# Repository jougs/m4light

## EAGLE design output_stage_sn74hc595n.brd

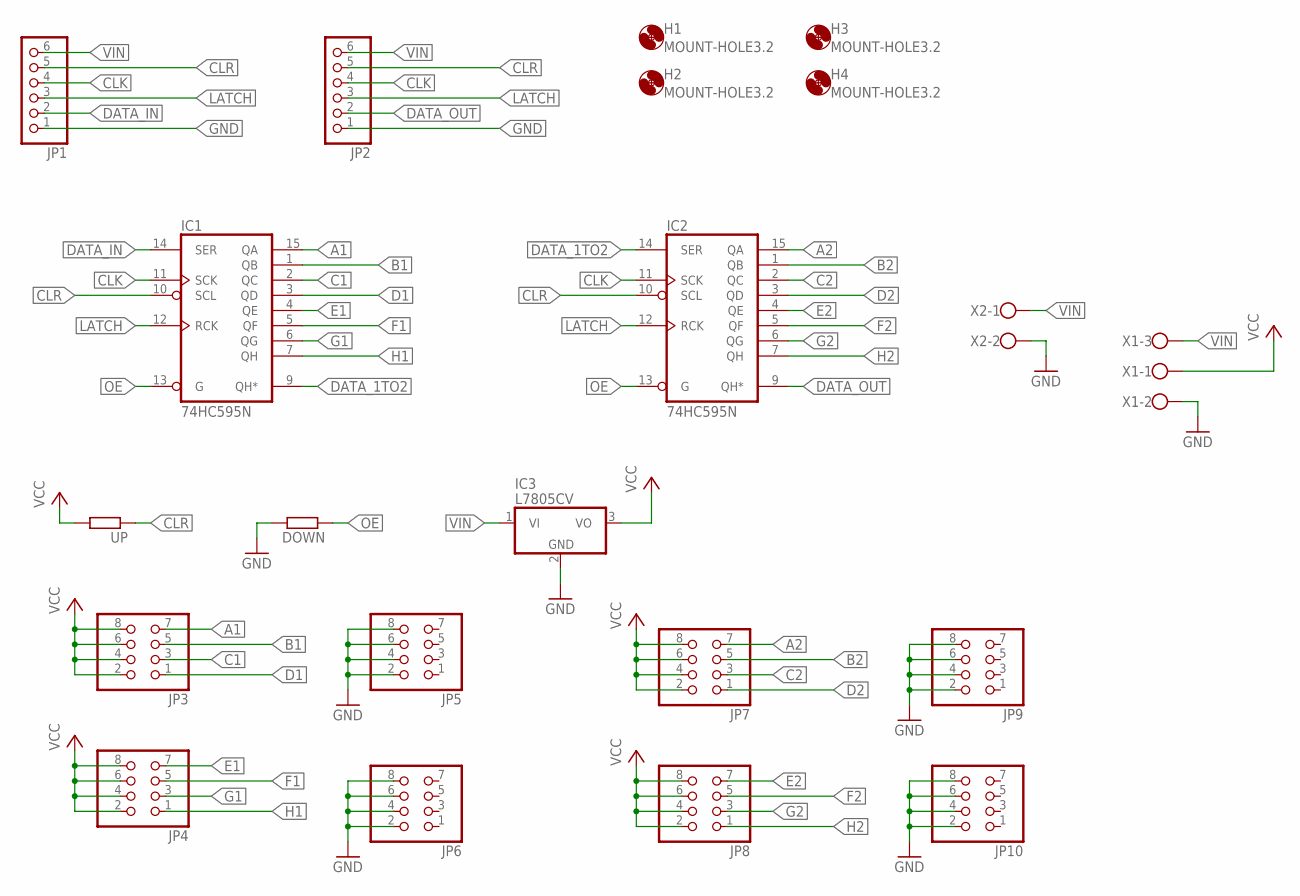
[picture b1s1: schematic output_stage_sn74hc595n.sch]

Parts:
DOWN: R-EU_0207/10; 0207/10
H1, H2, H3, H4: MOUNT-HOLE3.2; 3,2
IC1, IC2: 74HC595N; DIL16
IC3: L7805CV; TO220V
JP1, JP2: PINHD-1X6; 1X06
JP3, JP4, JP5, JP6, JP7, JP8, JP9, JP10: PINHD-2X4; 2X04
UP: R-EU_0207/10; 0207/10
X1: W237-103
X2: W237-102

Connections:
A1: IC1.15 (QA), JP3.7
A2: IC2.15 (QA), JP7.7
B1: IC1.1 (QB), JP3.5
B2: IC2.1 (QB), JP7.5
C1: IC1.2 (QC), JP3.3
C2: IC2.2 (QC), JP7.3
CLK: IC1.11 (SCK), IC2.11 (SCK), JP1.4, JP2.4
CLR: IC1.10 (SCL), IC2.10 (SCL), JP1.5, JP2.5, UP.1
D1: IC1.3 (QD), JP3.1
D2: IC2.3 (QD), JP7.1
DATA_1TO2: IC1.9 (QH*), IC2.14 (SER)
DATA_IN: IC1.14 (SER), JP1.2
DATA_OUT: IC2.9 (QH*), JP2.2
E1: IC1.4 (QE), JP4.7
E2: IC2.4 (QE), JP8.7
F1: IC1.5 (QF), JP4.5
F2: IC2.5 (QF), JP8.5
G1: IC1.6 (QG), JP4.3
G2: IC2.6 (QG), JP8.3
GND: DOWN.2, IC1.8 (GND), IC2.8 (GND), IC3.2 (GND), JP1.1, JP2.1, JP5.2, JP5.4, JP5.6, JP5.8, JP6.2, JP6.4, JP6.6, JP6.8, JP9.2, JP9.4, JP9.6, JP9.8, JP10.2, JP10.4, JP10.6, JP10.8, X1.2, X2.2
H1: IC1.7 (QH), JP4.1
H2: IC2.7 (QH), JP8.1
LATCH: IC1.12 (RCK), IC2.12 (RCK), JP1.3, JP2.3
OE: DOWN.1, IC1.13 (G), IC2.13 (G)
VCC: IC1.16 (VCC), IC2.16 (VCC), IC3.3 (VO), JP3.2, JP3.4, JP3.6, JP3.8, JP4.2, JP4.4, JP4.6, JP4.8, JP7.2, JP7.4, JP7.6, JP7.8, JP8.2, JP8.4, JP8.6, JP8.8, UP.2, X1.1
VIN: IC3.1 (VI), JP1.6, JP2.6, X1.3, X2.1

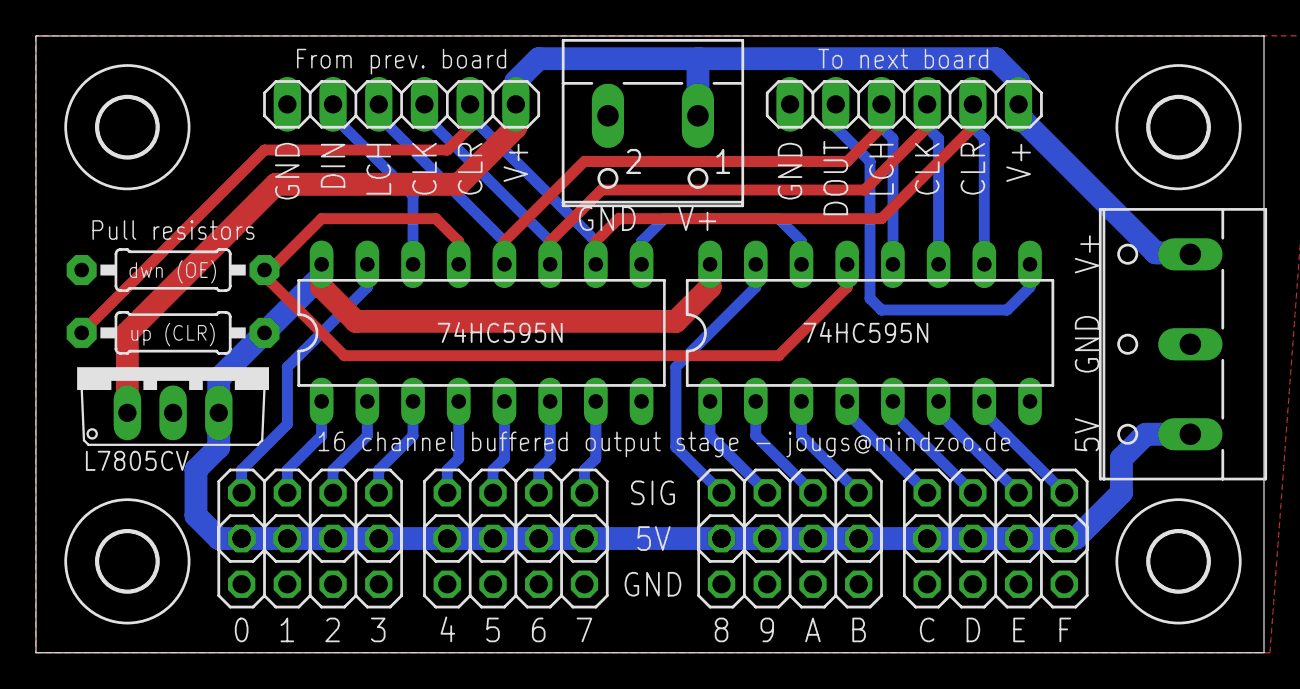
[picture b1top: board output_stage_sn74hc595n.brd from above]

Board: 2 copper layers, 68.2 x 34.3 mm, 21 parts (0 on the bottom side), 26 nets.

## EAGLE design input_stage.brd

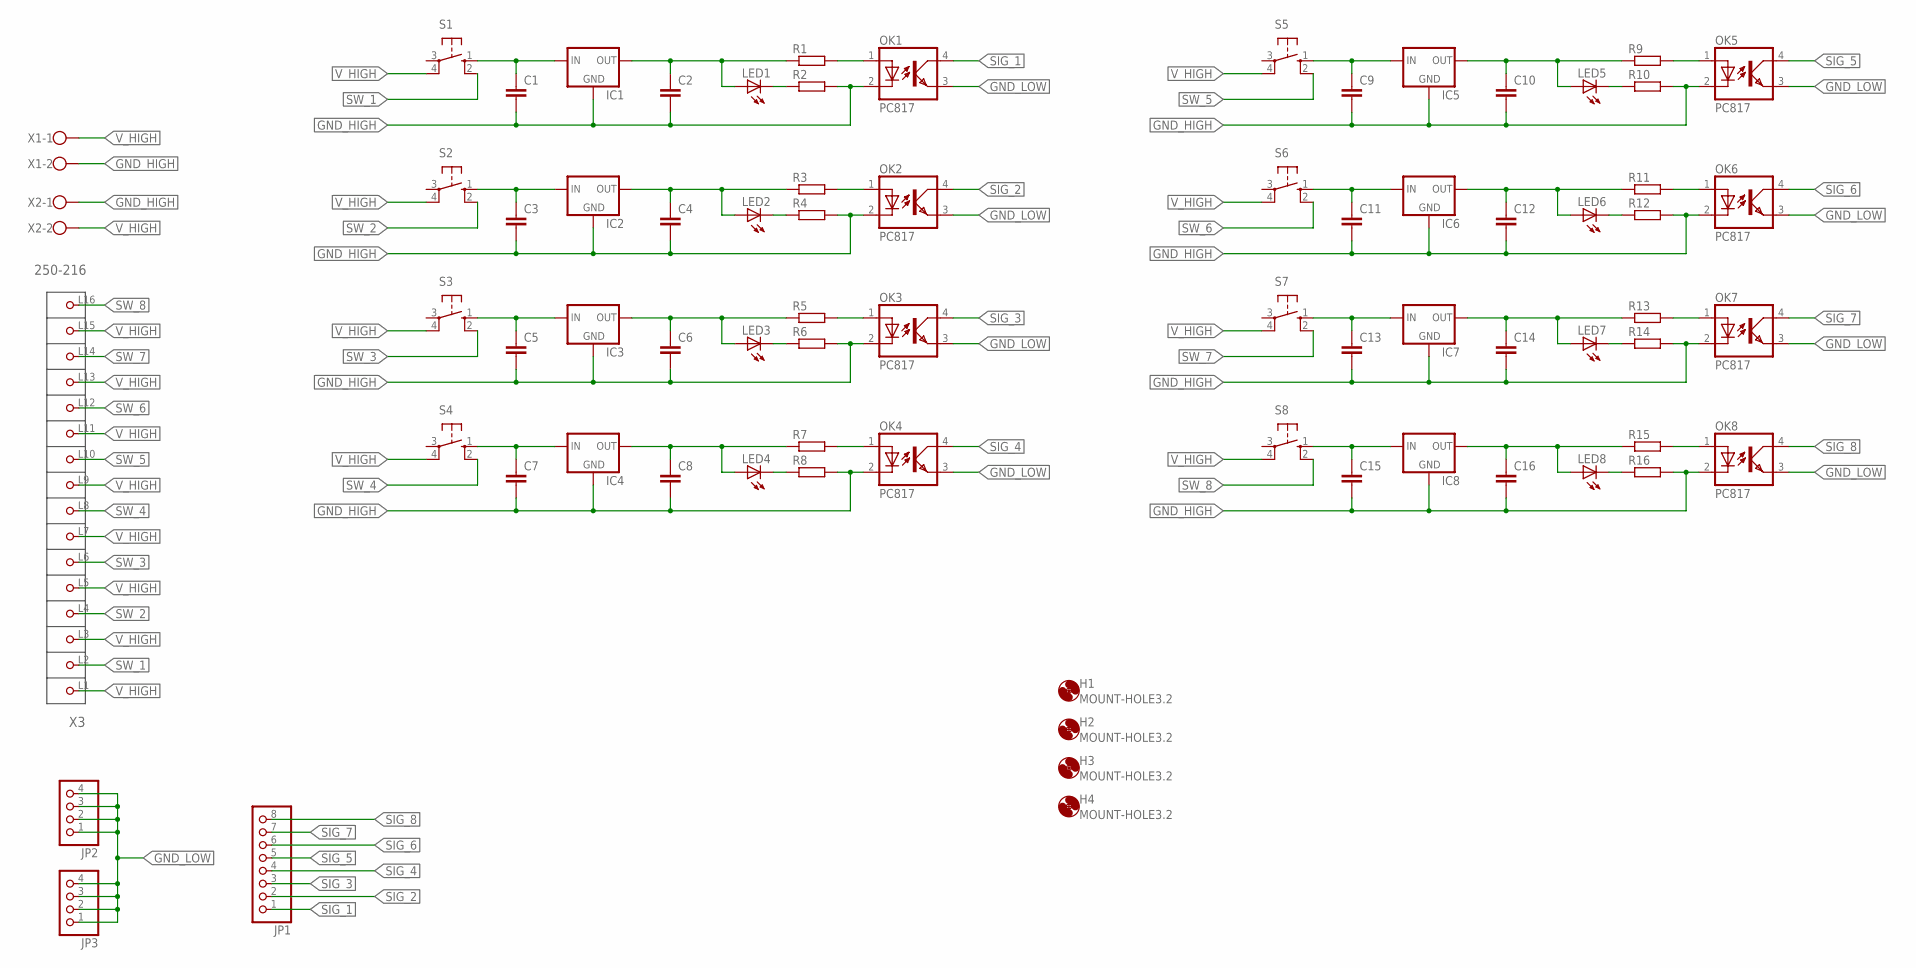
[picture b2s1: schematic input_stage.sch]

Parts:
C1, C2, C3, C4, C5, C6, C7, C8, C9, C10, C11, C12, C13, C14, C15, C16: C-EU050-024X044; C050-024X044
H1, H2, H3, H4: MOUNT-HOLE3.2; 3,2
IC1, IC2, IC3, IC4, IC5, IC6, IC7, IC8: 78LXX
JP1: PINHD-1X8; 1X08
JP2, JP3: PINHD-1X4; 1X04
LED1, LED2, LED3, LED4, LED5, LED6, LED7, LED8: LED3MM
OK1, OK2, OK3, OK4, OK5, OK6, OK7, OK8: PC817; DIL04
R1, R2, R3, R4, R5, R6, R7, R8, R9, R10, R11, R12, R13, R14, R15, R16: R-EU_0207/10; 0207/10
S1, S2, S3, S4, S5, S6, S7, S8: 10-XX; B3F-10XX
X1, X2: W237-102
X3: 250-216; P-250-216

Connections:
GND_HIGH: C1.2, C2.2, C3.2, C4.2, C5.2, C6.2, C7.2, C8.2, C9.2, C10.2, C11.2, C12.2, C13.2, C14.2, C15.2, C16.2, IC1.GND, IC2.GND, IC3.GND, IC4.GND, IC5.GND, IC6.GND, IC7.GND, IC8.GND, OK1.2 (C), OK2.2 (C), OK3.2 (C), OK4.2 (C), OK5.2 (C), OK6.2 (C), OK7.2 (C), OK8.2 (C), R2.2, R4.2, R6.2, R8.2, R10.2, R12.2, R14.2, R16.2, X1.2, X2.1
GND_LOW: JP2.1, JP2.2, JP2.3, JP2.4, JP3.1, JP3.2, JP3.3, JP3.4, OK1.3 (EMIT), OK2.3 (EMIT), OK3.3 (EMIT), OK4.3 (EMIT), OK5.3 (EMIT), OK6.3 (EMIT), OK7.3 (EMIT), OK8.3 (EMIT)
unnamed: OK1.1 (A), R1.2
unnamed: C2.1, IC1.OUT, LED1.A, R1.1
unnamed: C1.1, IC1.IN, S1.1 (S)
unnamed: LED1.K (C), R2.1
unnamed: OK4.1 (A), R7.2
unnamed: OK2.1 (A), R3.2
unnamed: C8.1, IC4.OUT, LED4.A, R7.1
unnamed: LED4.K (C), R8.1
unnamed: OK5.1 (A), R9.2
unnamed: C10.1, IC5.OUT, LED5.A, R9.1
unnamed: LED5.K (C), R10.1
unnamed: OK6.1 (A), R11.2
unnamed: C3.1, IC2.IN, S2.1 (S)
unnamed: C12.1, IC6.OUT, LED6.A, R11.1
unnamed: C5.1, IC3.IN, S3.1 (S)
unnamed: LED6.K (C), R12.1
unnamed: C7.1, IC4.IN, S4.1 (S)
unnamed: OK7.1 (A), R13.2
unnamed: C15.1, IC8.IN, S8.1 (S)
unnamed: C4.1, IC2.OUT, LED2.A, R3.1
unnamed: LED2.K (C), R4.1
unnamed: C14.1, IC7.OUT, LED7.A, R13.1
unnamed: OK3.1 (A), R5.2
unnamed: C6.1, IC3.OUT, LED3.A, R5.1
unnamed: LED3.K (C), R6.1
unnamed: LED7.K (C), R14.1
unnamed: OK8.1 (A), R15.2
unnamed: C16.1, IC8.OUT, LED8.A, R15.1
unnamed: LED8.K (C), R16.1
unnamed: C13.1, IC7.IN, S7.1 (S)
unnamed: C11.1, IC6.IN, S6.1 (S)
unnamed: C9.1, IC5.IN, S5.1 (S)
SIG_1: JP1.1, OK1.4 (COL)
SIG_2: JP1.2, OK2.4 (COL)
SIG_3: JP1.3, OK3.4 (COL)
SIG_4: JP1.4, OK4.4 (COL)
SIG_5: JP1.5, OK5.4 (COL)
SIG_6: JP1.6, OK6.4 (COL)
SIG_7: JP1.7, OK7.4 (COL)
SIG_8: JP1.8, OK8.4 (COL)
SW_1: S1.2 (S1), X3.L2 (P2)
SW_2: S2.2 (S1), X3.L4 (P4)
SW_3: S3.2 (S1), X3.L6 (P6)
SW_4: S4.2 (S1), X3.L8 (P8)
SW_5: S5.2 (S1), X3.L10 (P10)
SW_6: S6.2 (S1), X3.L12 (P12)
SW_7: S7.2 (S1), X3.L14 (P14)
SW_8: S8.2 (S1), X3.L16 (P16)
V_HIGH: S1.4 (P1), S2.4 (P1), S3.4 (P1), S4.4 (P1), S5.4 (P1), S6.4 (P1), S7.4 (P1), S8.4 (P1), X1.1, X2.2, X3.L1 (P1), X3.L3 (P3), X3.L5 (P5), X3.L7 (P7), X3.L9 (P9), X3.L11 (P11), X3.L13 (P13), X3.L15 (P15)

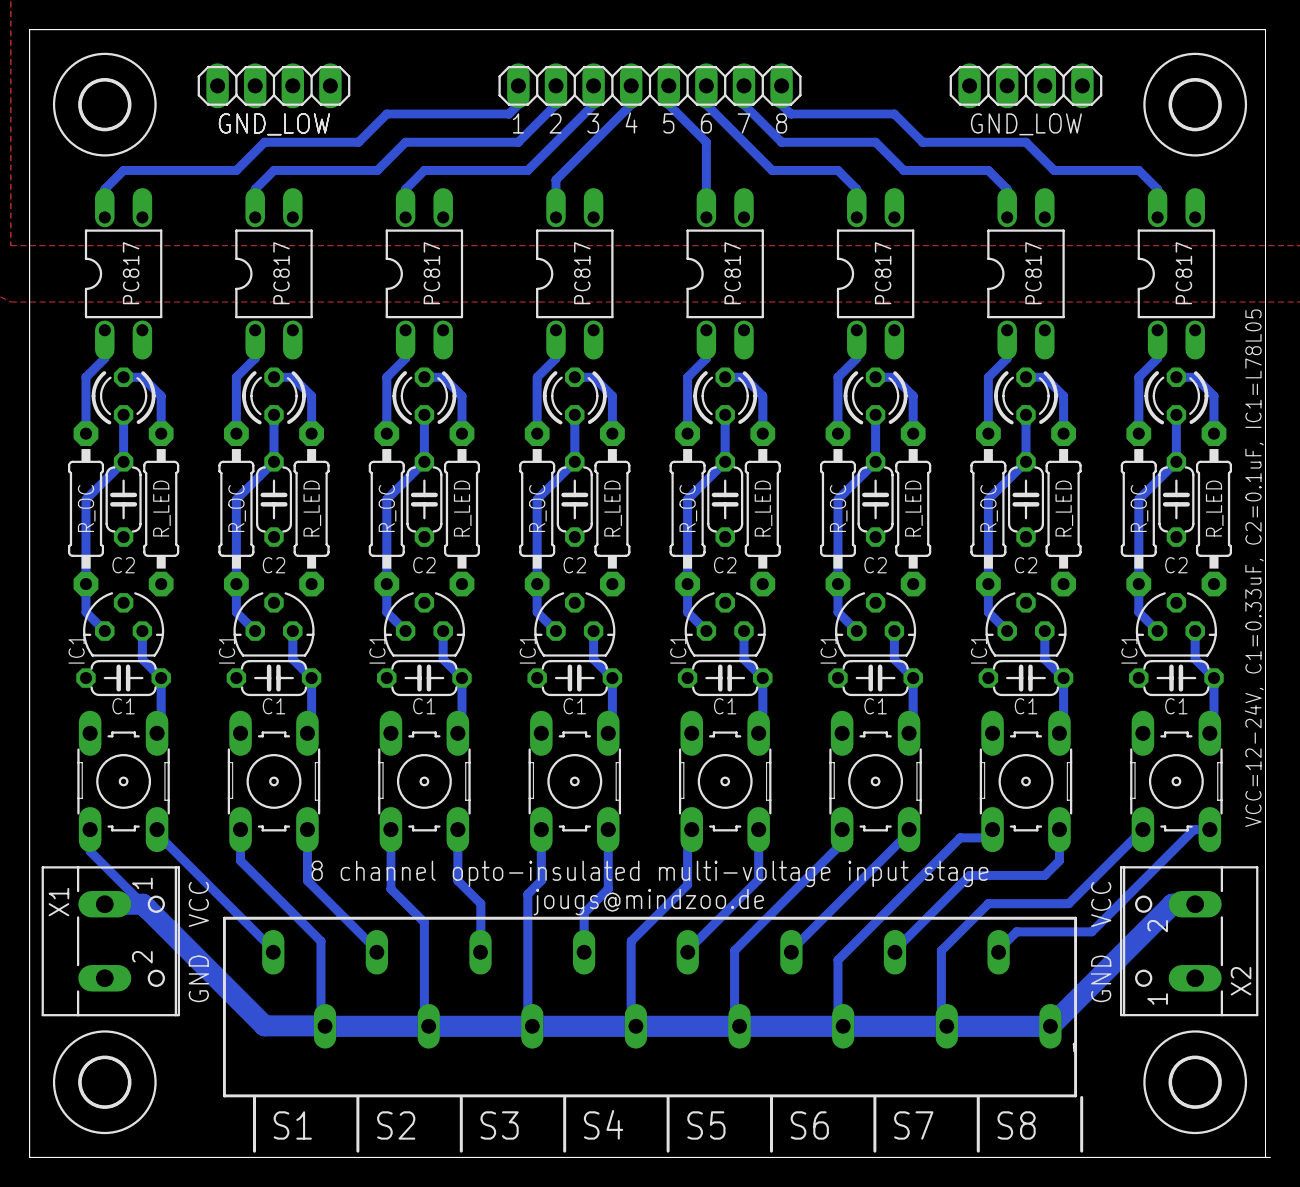
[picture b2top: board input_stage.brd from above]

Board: 2 copper layers, 83.8 x 76.2 mm, 74 parts (0 on the bottom side), 51 nets.

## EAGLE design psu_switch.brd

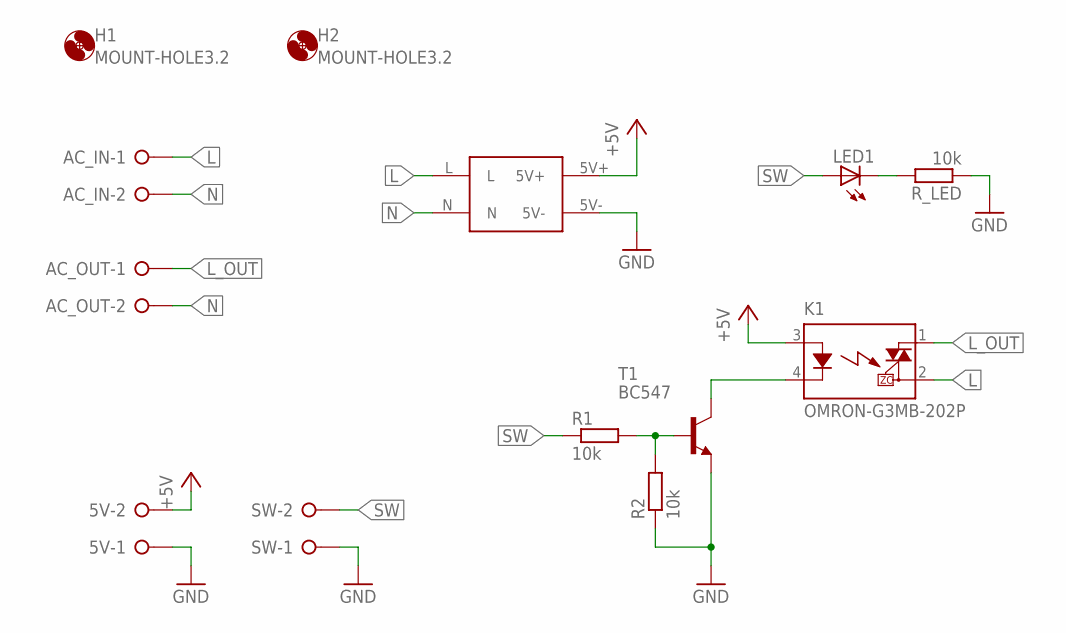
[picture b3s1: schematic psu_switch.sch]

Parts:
5V: W237-02P; W237-132
AC_IN: W237-02P; W237-132
AC_OUT: W237-02P; W237-132
H1, H2: MOUNT-HOLE3.2; 3,2
K1: OMRON-G3MB-202P; OMRON-G3MB-202P-SSR
LED1: LED3MM
R1, R2: 10k; 0207/10
R_LED: 10k; 0207/10
SW: W237-02P; W237-132
T1: BC547; TO92
U$1: 700MA-STEP-DOWN

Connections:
+5V: 5V.2, K1.3 (A), U$1.5V+
GND: 5V.1, R2.1, R_LED.1, SW.1, T1.1 (E), U$1.5V-
L: AC_IN.1, K1.2 (DS2), U$1.L
L_OUT: AC_OUT.1, K1.1 (DS1)
N: AC_IN.2, AC_OUT.2, U$1.N
unnamed: LED1.K (C), R_LED.2
unnamed: K1.4 (K), T1.3 (C)
SW: LED1.A, R1.1, SW.2
SW+: R1.2, R2.2, T1.2 (B)

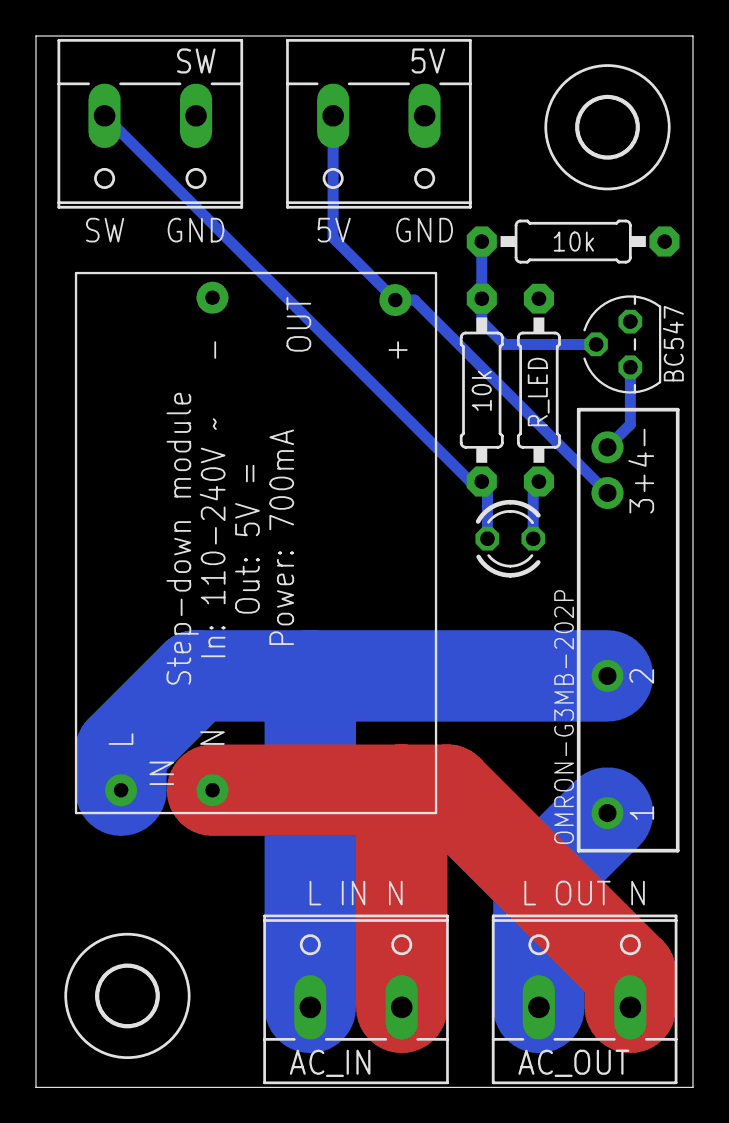
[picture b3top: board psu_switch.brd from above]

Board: 2 copper layers, 36.5 x 58.4 mm, 13 parts (0 on the bottom side), 9 nets.

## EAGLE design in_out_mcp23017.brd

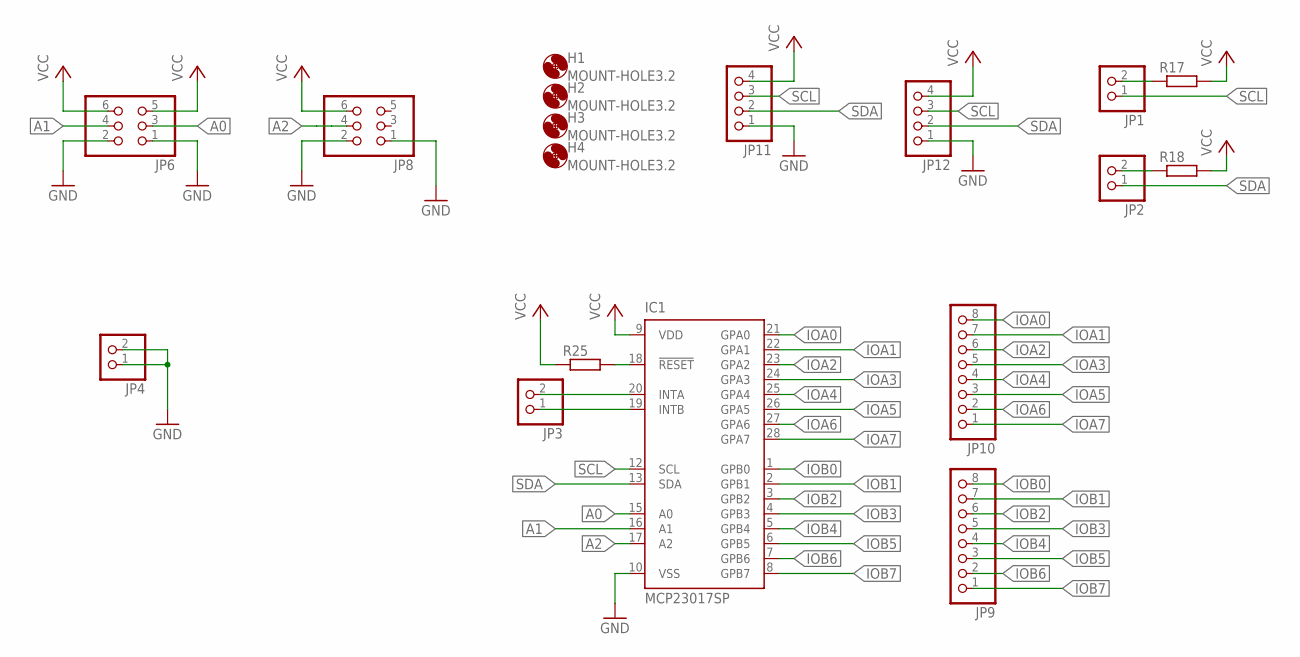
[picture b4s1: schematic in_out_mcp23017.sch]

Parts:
H1, H2, H3, H4: MOUNT-HOLE3.2; 3,2
IC1: MCP23017SP; DIL28-3
JP1, JP2, JP3, JP4: PINHD-1X2; 1X02
JP6, JP8: PINHD-2X3; 2X03
JP9, JP10: PINHD-1X8; 1X08
JP11, JP12: PINHD-1X4; 1X04
R17, R18, R25: R-EU_0207/10; 0207/10

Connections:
A0: IC1.15 (A0), JP6.3
A1: IC1.16 (A1), JP6.4
A2: IC1.17 (A2), JP8.4
GND: IC1.10 (VSS), JP4.1, JP4.2, JP6.1, JP6.2, JP8.1, JP8.2, JP11.1, JP12.1
IOA0: IC1.21 (GPA0), JP10.8
IOA1: IC1.22 (GPA1), JP10.7
IOA2: IC1.23 (GPA2), JP10.6
IOA3: IC1.24 (GPA3), JP10.5
IOA4: IC1.25 (GPA4), JP10.4
IOA5: IC1.26 (GPA5), JP10.3
IOA6: IC1.27 (GPA6), JP10.2
IOA7: IC1.28 (GPA7), JP10.1
IOB0: IC1.1 (GPB0), JP9.8
IOB1: IC1.2 (GPB1), JP9.7
IOB2: IC1.3 (GPB2), JP9.6
IOB3: IC1.4 (GPB3), JP9.5
IOB4: IC1.5 (GPB4), JP9.4
IOB5: IC1.6 (GPB5), JP9.3
IOB6: IC1.7 (GPB6), JP9.2
IOB7: IC1.8 (GPB7), JP9.1
unnamed: IC1.18 (!RESET), R25.2
unnamed: JP2.2, R18.1
unnamed: JP1.2, R17.1
unnamed: IC1.20 (INTA), JP3.2
unnamed: IC1.19 (INTB), JP3.1
SCL: IC1.12 (SCL), JP1.1, JP11.3, JP12.3
SDA: IC1.13 (SDA), JP2.1, JP11.2, JP12.2
VCC: IC1.9 (VDD), JP6.5, JP6.6, JP8.6, JP11.4, JP12.4, R17.2, R18.2, R25.1

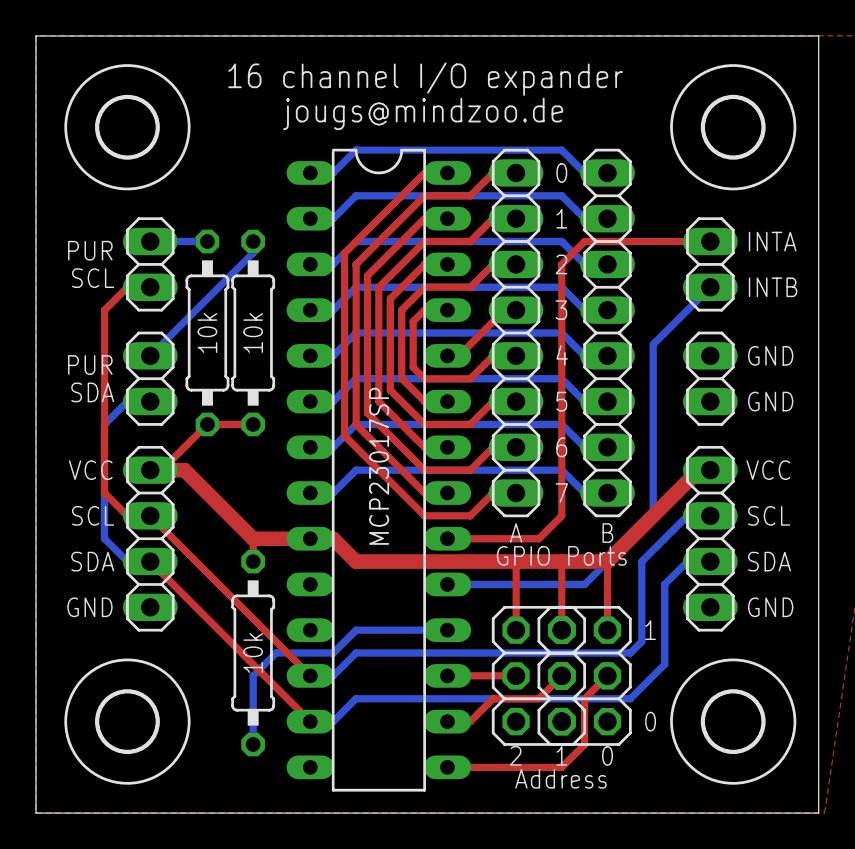
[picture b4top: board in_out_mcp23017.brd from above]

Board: 2 copper layers, 43.5 x 43.2 mm, 18 parts (0 on the bottom side), 28 nets.

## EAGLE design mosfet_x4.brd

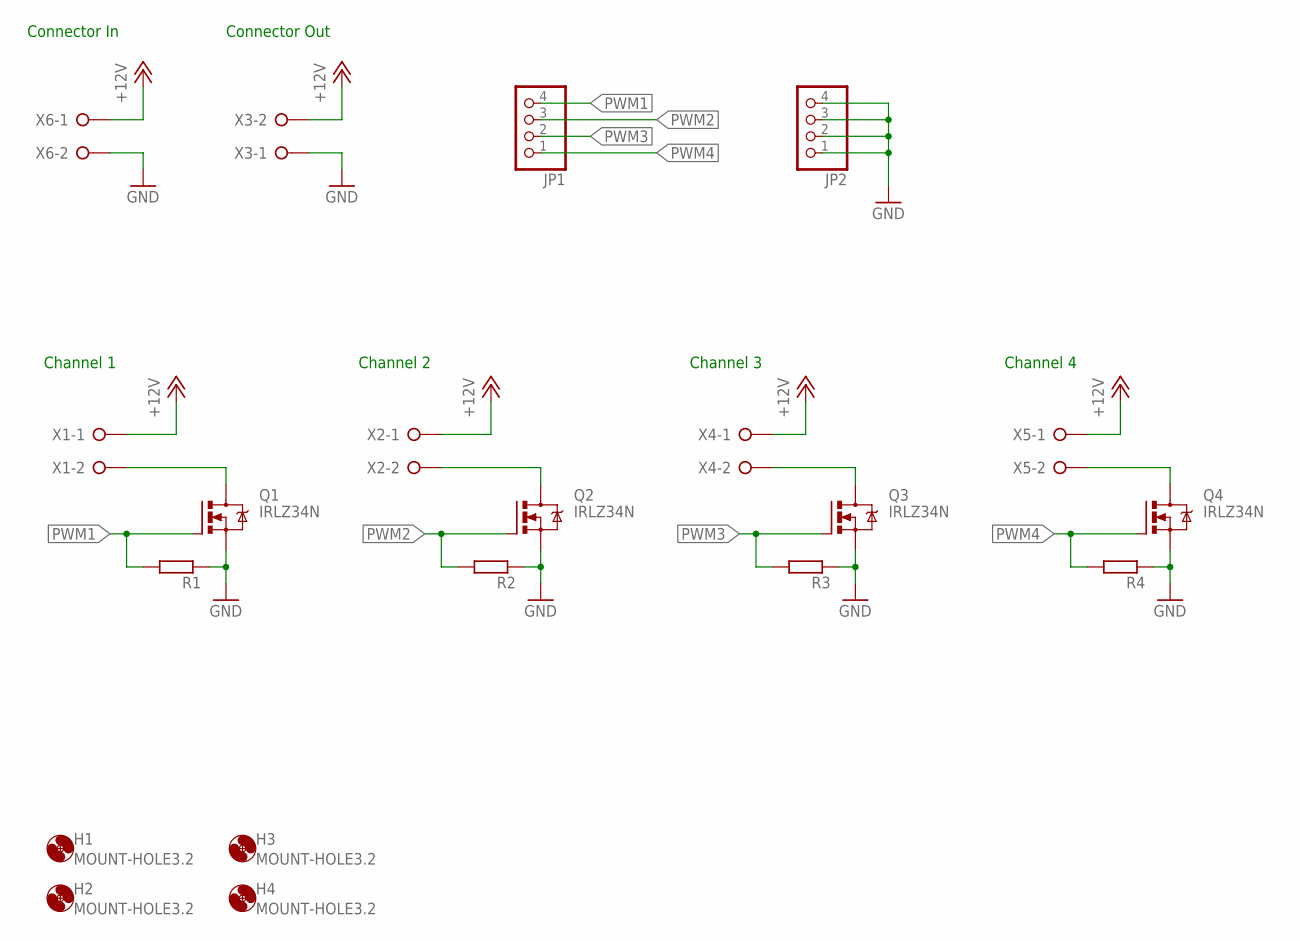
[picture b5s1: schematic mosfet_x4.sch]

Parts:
H1, H2, H3, H4: MOUNT-HOLE3.2; 3,2
JP1, JP2: PINHD-1X4; 1X04
Q1, Q2, Q3, Q4: IRLZ34N; TO220BV
R1, R2, R3, R4: R-EU_0207/10; 0207/10
X1, X2, X3, X4, X5, X6: W237-02P; W237-132

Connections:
+12V: X1.1, X2.1, X3.2, X4.1, X5.1, X6.1
GND: JP2.1, JP2.2, JP2.3, JP2.4, Q1.S, Q2.S, Q3.S, Q4.S, R1.1, R2.1, R3.1, R4.1, X3.1, X6.2
unnamed: Q1.D, X1.2
unnamed: Q2.D, X2.2
unnamed: Q3.D, X4.2
unnamed: Q4.D, X5.2
PWM1: JP1.4, Q1.G, R1.2
PWM2: JP1.3, Q2.G, R2.2
PWM3: JP1.2, Q3.G, R3.2
PWM4: JP1.1, Q4.G, R4.2

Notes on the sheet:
Channel 1
Channel 2
Channel 3
Channel 4
Connector In
Connector Out

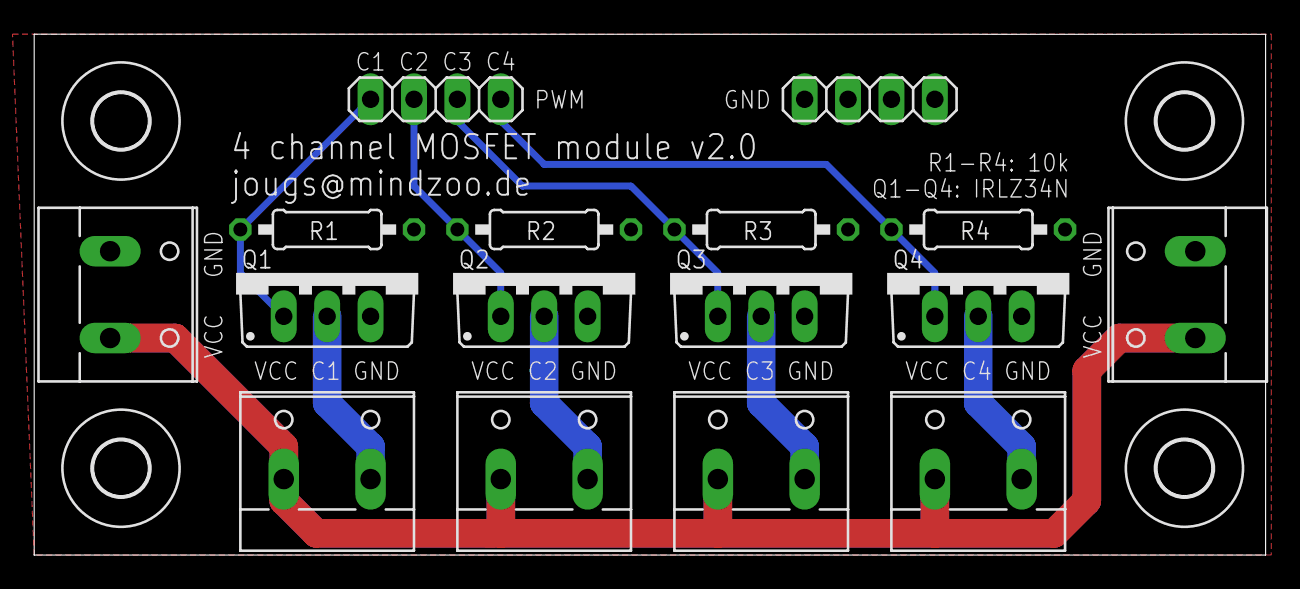
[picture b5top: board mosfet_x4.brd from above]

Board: 2 copper layers, 72.1 x 30.5 mm, 20 parts (0 on the bottom side), 10 nets.

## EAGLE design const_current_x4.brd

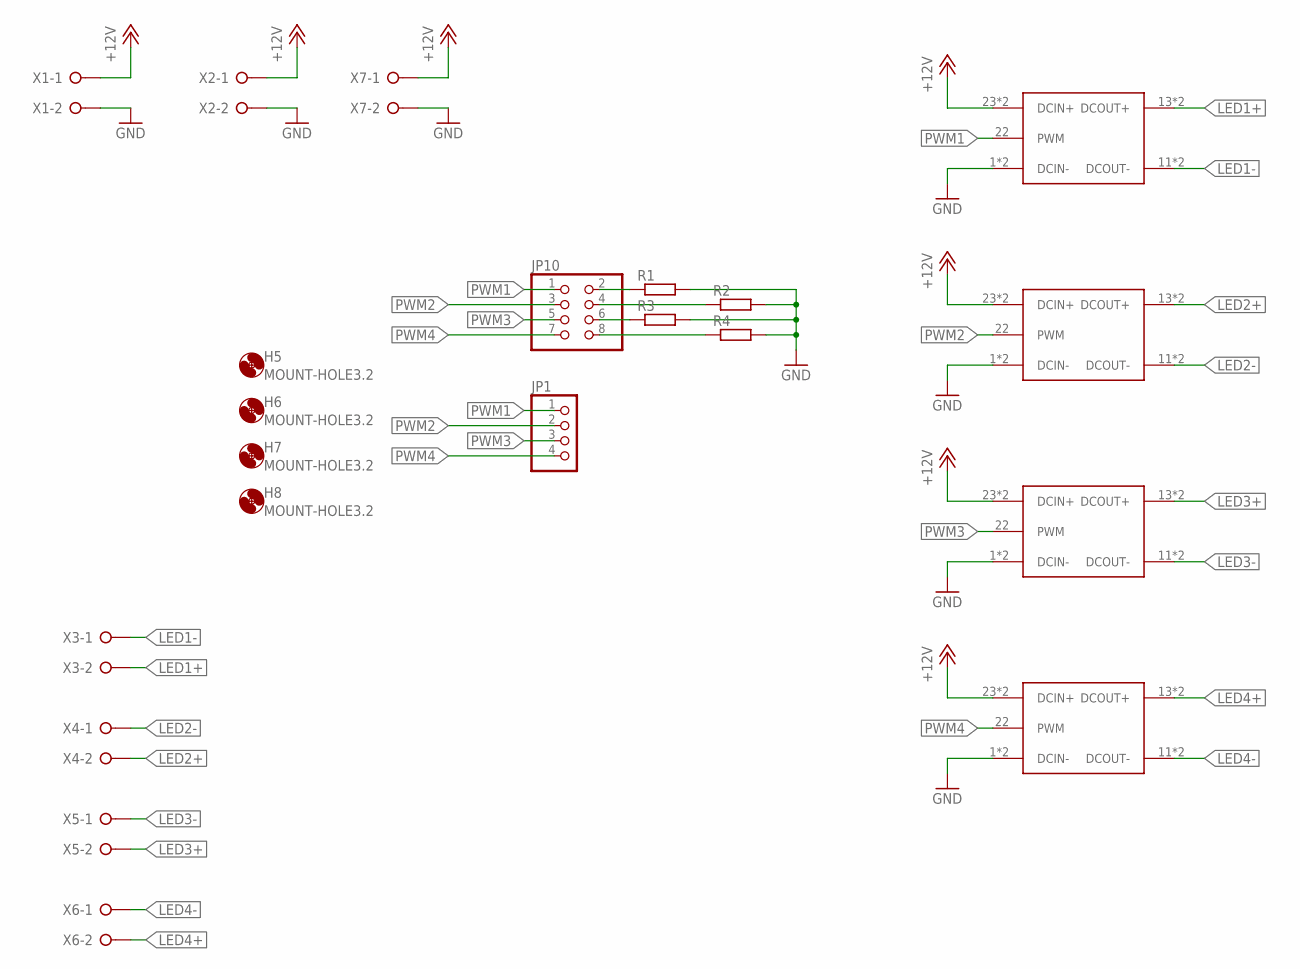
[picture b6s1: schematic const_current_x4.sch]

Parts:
H5, H6, H7, H8: MOUNT-HOLE3.2; 3,2
JP1: PINHD-1X4; 1X04
JP10: PINHD-2X4; 2X04
R1, R2, R3, R4: R-EU_0207/10; 0207/10
U$5, U$6, U$7, U$8: LDD_H
X1, X2, X3, X4, X5, X6, X7: W237-02P; W237-132

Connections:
+12V: U$5.23 (DCIN+), U$5.24 (DCIN+), U$6.23 (DCIN+), U$6.24 (DCIN+), U$7.23 (DCIN+), U$7.24 (DCIN+), U$8.23 (DCIN+), U$8.24 (DCIN+), X1.1, X2.1, X7.1
GND: R1.2, R2.2, R3.2, R4.2, U$5.1 (DCIN-), U$5.2 (DCIN-), U$6.1 (DCIN-), U$6.2 (DCIN-), U$7.1 (DCIN-), U$7.2 (DCIN-), U$8.1 (DCIN-), U$8.2 (DCIN-), X1.2, X2.2, X7.2
LED1+: U$5.13 (DCOUT+), U$5.14 (DCOUT+), X3.2
LED1-: U$5.11 (DCOUT-), U$5.12 (DCOUT-), X3.1
LED2+: U$6.13 (DCOUT+), U$6.14 (DCOUT+), X4.2
LED2-: U$6.11 (DCOUT-), U$6.12 (DCOUT-), X4.1
LED3+: U$7.13 (DCOUT+), U$7.14 (DCOUT+), X5.2
LED3-: U$7.11 (DCOUT-), U$7.12 (DCOUT-), X5.1
LED4+: U$8.13 (DCOUT+), U$8.14 (DCOUT+), X6.2
LED4-: U$8.11 (DCOUT-), U$8.12 (DCOUT-), X6.1
unnamed: JP10.2, R1.1
unnamed: JP10.4, R2.1
unnamed: JP10.6, R3.1
unnamed: JP10.8, R4.1
PWM1: JP1.1, JP10.1, U$5.22 (PWM)
PWM2: JP1.2, JP10.3, U$6.22 (PWM)
PWM3: JP1.3, JP10.5, U$7.22 (PWM)
PWM4: JP1.4, JP10.7, U$8.22 (PWM)

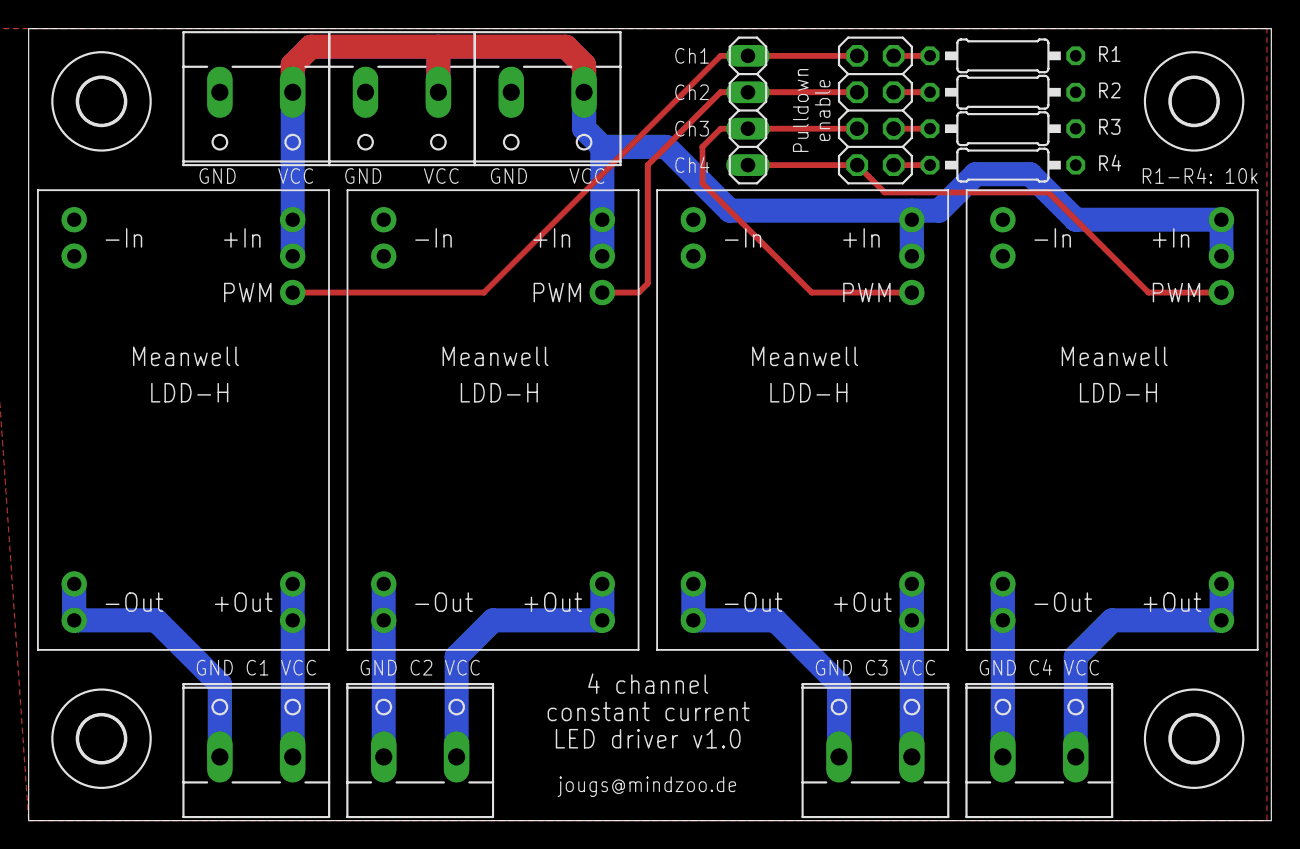
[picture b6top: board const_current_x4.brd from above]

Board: 2 copper layers, 86.7 x 55.2 mm, 21 parts (0 on the bottom side), 18 nets.

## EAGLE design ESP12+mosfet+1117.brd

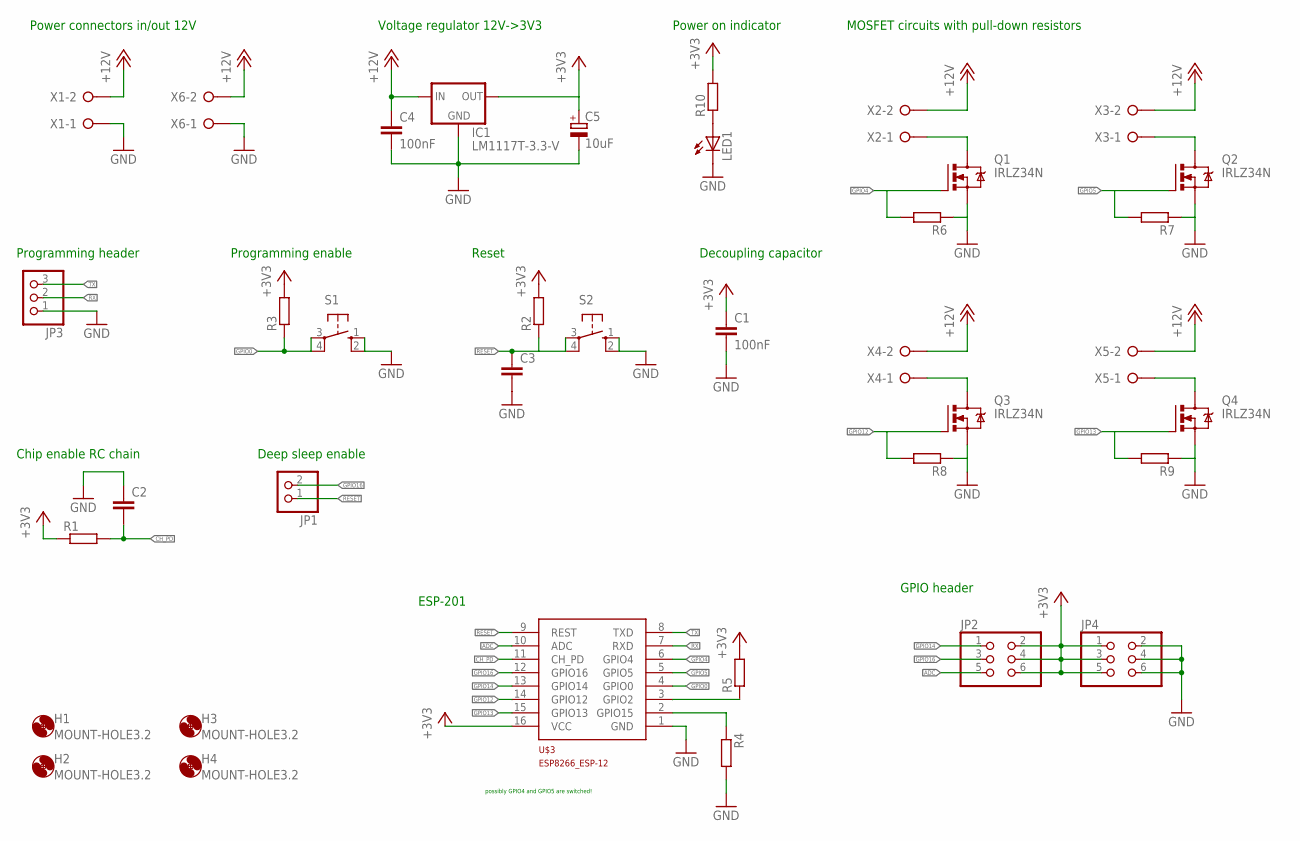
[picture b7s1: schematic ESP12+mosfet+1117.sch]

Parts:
C1, C4: 100nF; C0805
C2, C3: C-EUC0805; C0805
C5: 10uF; E2-4
H1, H2, H3, H4: MOUNT-HOLE3.2; 3,2
IC1: LM1117T-3.3-V; TO220V
JP1: PINHD-1X2; 1X02
JP2, JP4: PINHD-2X3; 2X03
JP3: PINHD-1X3; 1X03
LED1: LED3MM
Q1, Q2, Q3, Q4: IRLZ34N; TO220BV
R1, R2, R3, R4, R5, R6, R7, R8, R9: R-EU_R0805; R0805
R10: R-EU_0207/10; 0207/10
S1, S2: 10-XX; B3F-10XX
U$3: ESP8266_ESP-12; ESP8266-ESP12
X1, X2, X3, X4, X5, X6: W237-02P; W237-132

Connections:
+3V3: C1.1, C5.+, IC1.2 (OUT), JP2.2, JP2.4, JP2.6, JP4.1, JP4.3, JP4.5, R1.1, R2.2, R3.2, R5.2, R10.2, U$3.16 (VCC)
+12V: C4.1, IC1.3 (IN), X1.2, X2.2, X3.2, X4.2, X5.2, X6.2
ADC: JP2.5, U$3.10 (ADC)
CH_PD: C2.2, R1.2, U$3.11 (CH_PD)
GND: C1.2, C2.1, C3.2, C4.2, C5.-, IC1.1 (GND), JP3.1, JP4.2, JP4.4, JP4.6, LED1.K (C), Q1.S, Q2.S, Q3.S, Q4.S, R4.2, R6.1, R7.1, R8.1, R9.1, S1.1 (S), S1.2 (S1), S2.1 (S), S2.2 (S1), U$3.1 (GND), X1.1, X6.1
GPIO0: R3.1, S1.3, S1.4 (P1), U$3.4 (GPIO0)
GPIO1: R5.1, U$3.3 (GPIO2)
GPIO4: Q1.G, R6.2, U$3.6 (GPIO4)
GPIO5: Q2.G, R7.2, U$3.5 (GPIO5)
GPIO12: Q3.G, R8.2, U$3.14 (GPIO12)
GPIO13: Q4.G, R9.2, U$3.15 (GPIO13)
GPIO14: JP2.1, U$3.13 (GPIO14)
GPIO15: R4.1, U$3.2 (GPIO15)
GPIO16: JP1.2, JP2.3, U$3.12 (GPIO16)
unnamed: LED1.A, R10.1
unnamed: Q1.D, X2.1
unnamed: Q2.D, X3.1
unnamed: Q3.D, X4.1
unnamed: Q4.D, X5.1
RESET: C3.1, JP1.1, R2.1, S2.3, S2.4 (P1), U$3.9 (REST)
RX: JP3.2, U$3.7 (RXD)
TX: JP3.3, U$3.8 (TXD)

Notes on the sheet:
Power connectors in/out 12V
Voltage regulator 12V->3V3
Decoupling capacitor
Programming header
Chip enable RC chain
Programming enable
ESP-201
GPIO header
Reset
possibly GPIO4 and GPIO5 are switched!
Deep sleep enable
Power on indicator
MOSFET circuits with pull-down resistors

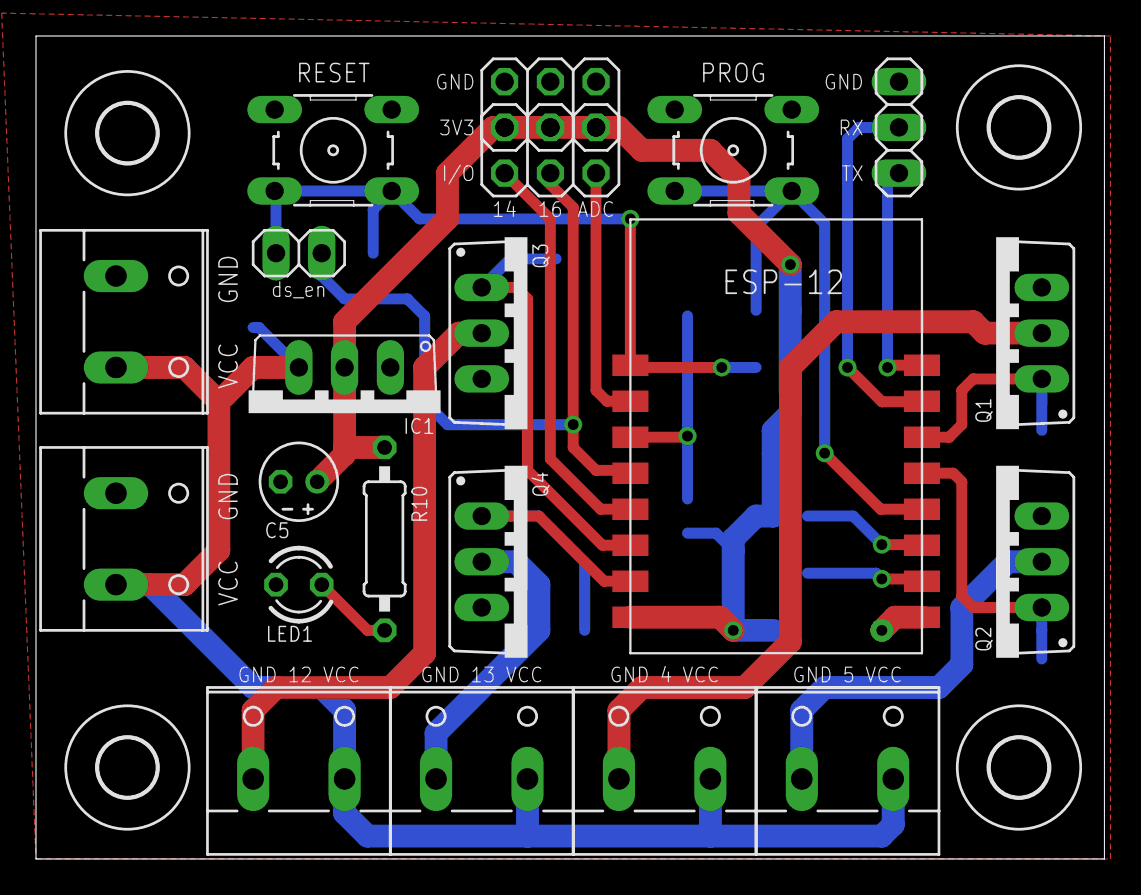
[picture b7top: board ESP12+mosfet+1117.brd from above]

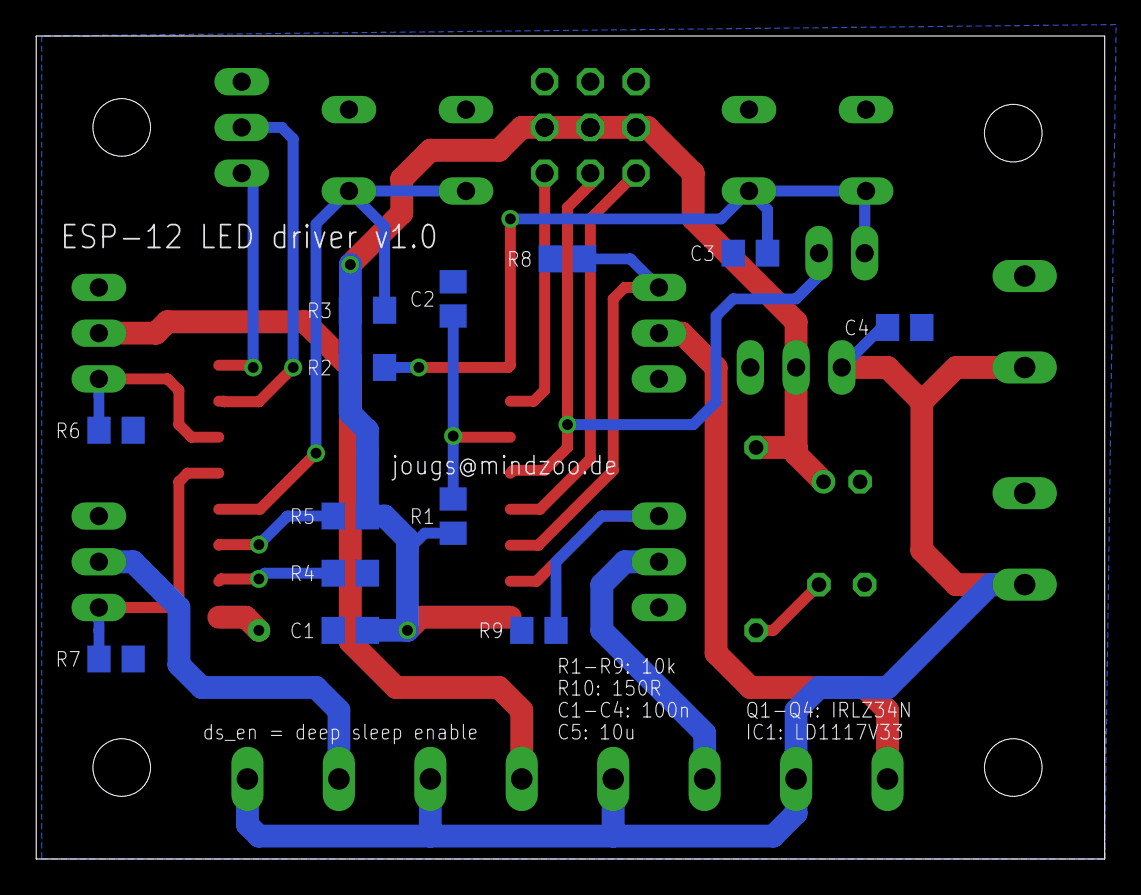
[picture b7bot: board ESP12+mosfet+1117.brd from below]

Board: 2 copper layers, 59.4 x 45.7 mm, 38 parts (13 on the bottom side), 22 nets.
